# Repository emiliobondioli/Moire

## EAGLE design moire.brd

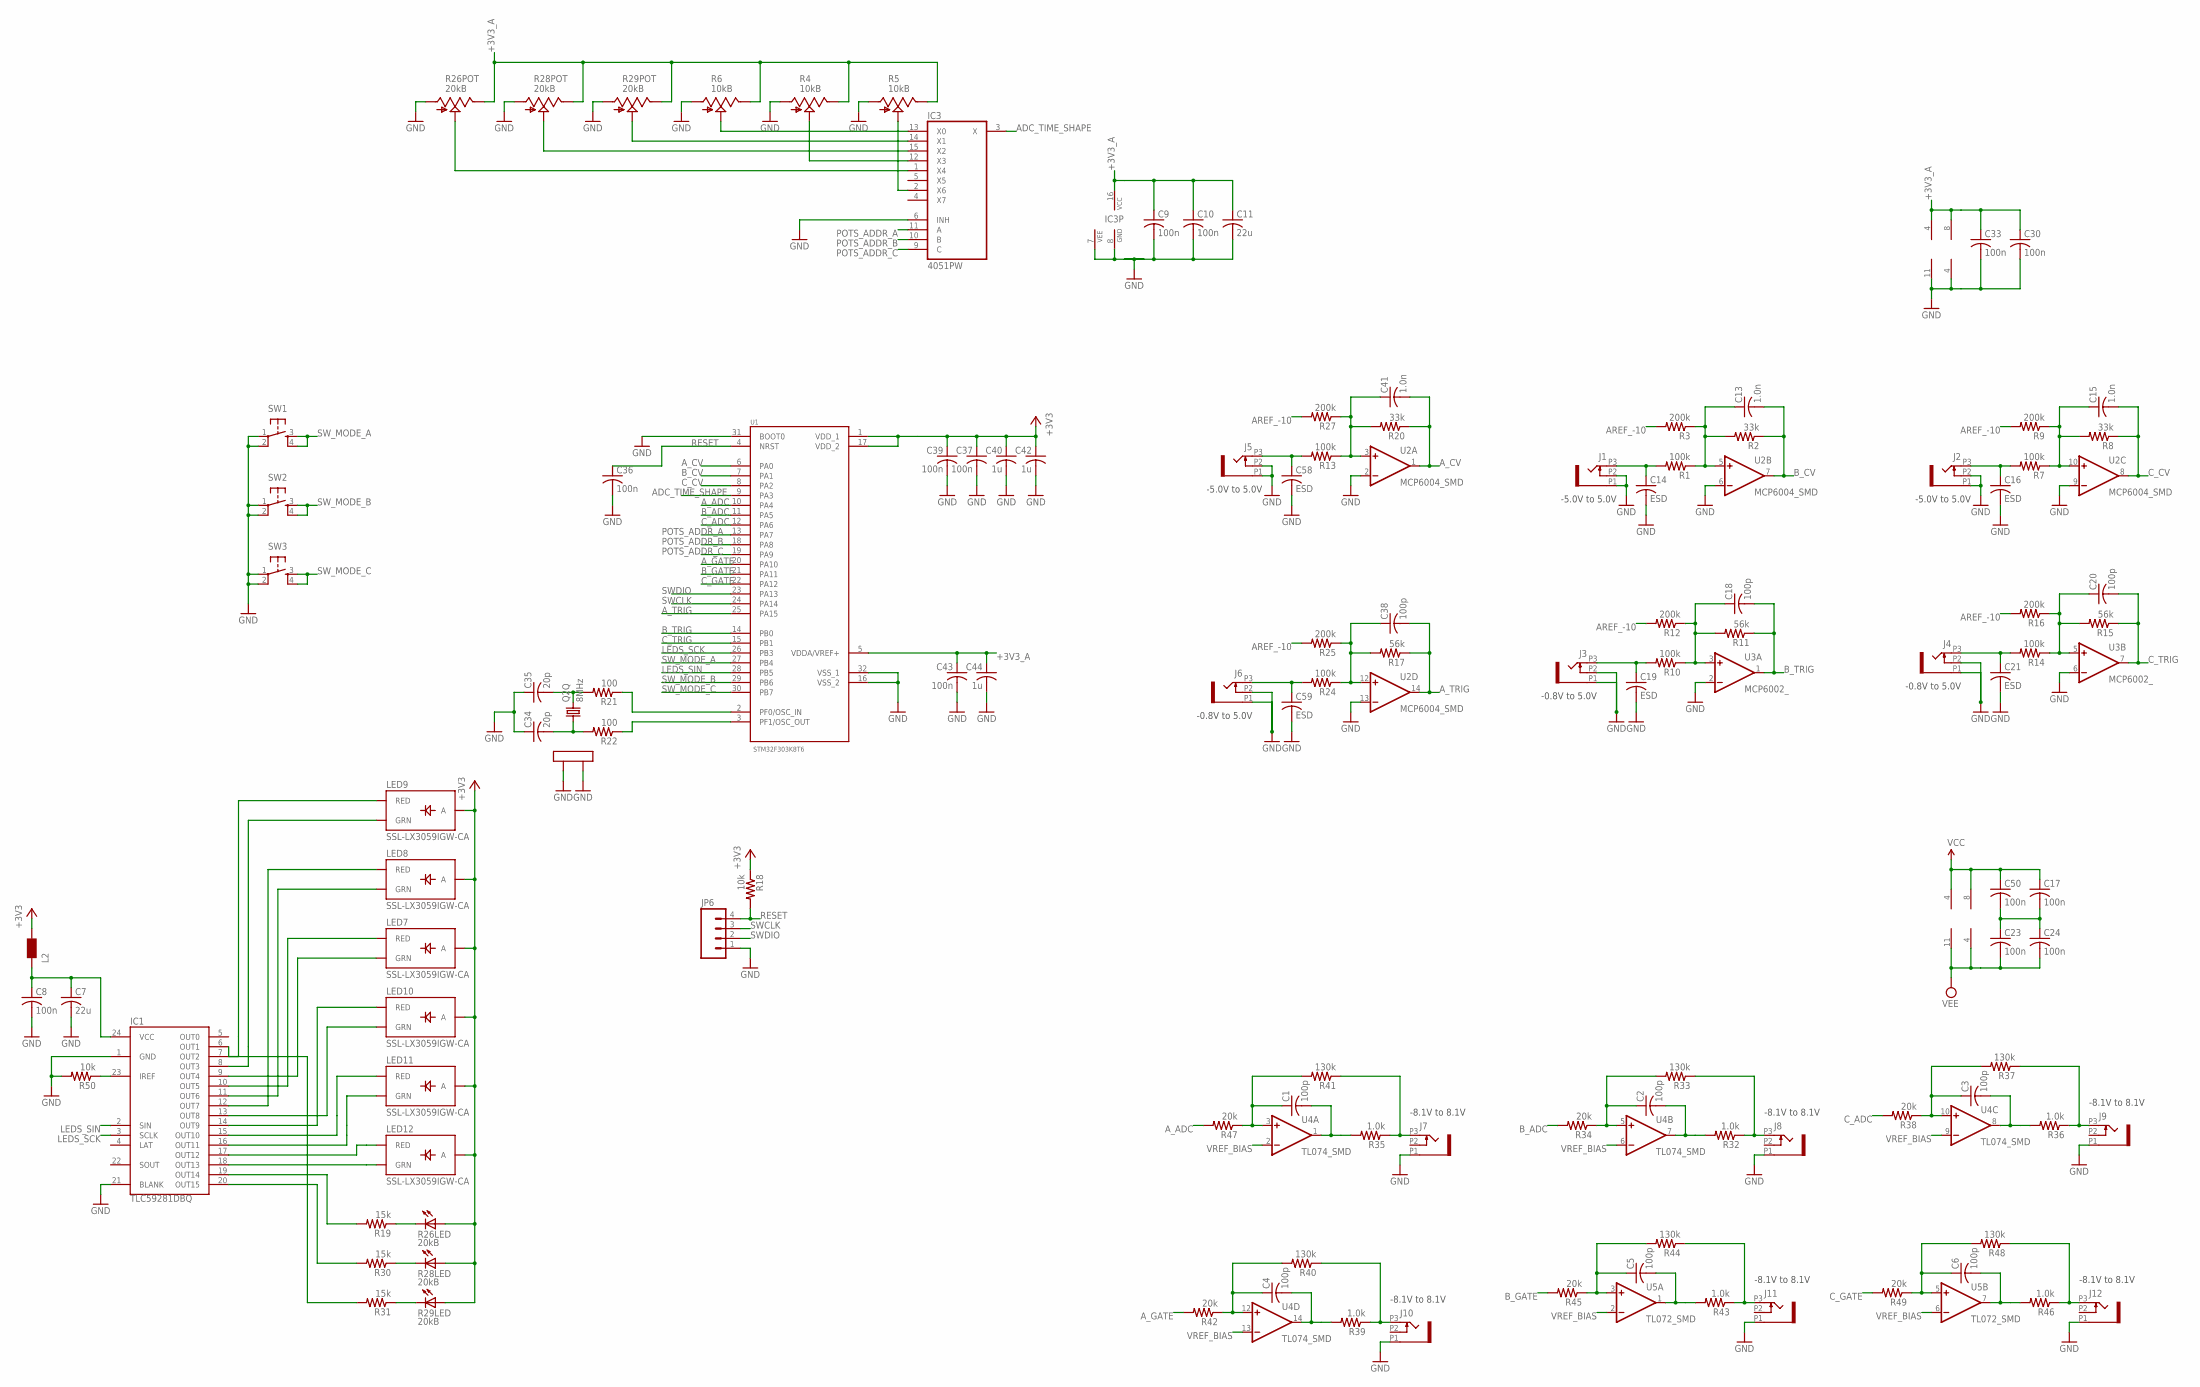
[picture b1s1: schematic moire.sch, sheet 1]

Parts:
C1, C2, C3, C4, C5, C6, C18, C20, C38: 100p; C0402
C7, C11: 22u; C1206
C8, C9, C10, C17, C23, C24, C30, C33, C36, C37, C39, C43, C50: 100n; C0402
C13, C15, C41: 1.0n; C0402
C14, C16, C19, C21, C58, C59: ESD; C0603
C34, C35: 20p; C0402
C40, C42, C44: 1u; C0402
IC1: TLC59281DBQ; TSSOP24_0635
IC3: 4051PW; TSSOP16_065
J1, J2, J3, J4, J5, J6, J7, J8, J9, J10, J11, J12: PJ301_THONKICONN6; WQP_PJ_301M6
JP6: M04PTH; 1X04
L2: WE-CBF_0603; 0603
LED7, LED8, LED9, LED10, LED11, LED12: SSL-LX3059IGW-CA; LED-BICOLOR-THROUGHHOLE-LUMEX
Q2: 8MHz; CTS406
R1, R7, R10, R13, R14, R24: 100k; R0402
R2, R8, R20: 33k; R0402
R3, R9, R12, R16, R25, R27: 200k; R0402
R4, R5, R6: 10kB; ALPS_POT_VERTICAL_PS
R11, R15, R17: 56k; R0402
R18, R50: 10k; R0402
R19, R30, R31: 15k; R0402
R21, R22: 100; R0402
R26, R28, R29: 20kB; BOURNS_SLIDER
R32, R35, R36, R39, R43, R46: 1.0k; R0603
R33, R37, R40, R41, R44, R48: 130k; R0402
R34, R38, R42, R45, R47, R49: 20k; R0402
SW1, SW2, SW3: TAC_SWITCHPTH; TACTILE-PTH
U1: STM32F303K8T6; QFP80P900X900X160-32N
U2: MCP6004_SMD; SO14
U3: MCP6002_; SO08
U4: TL074_SMD; SO14
U5: TL072_SMD; SO08

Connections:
+3V3_A: C9.1, C10.1, C11.1, C30.1, C33.1, C43.1, C44.1, IC3.16 (VCC), R4.P$1 (E), R5.P$1 (E), R6.P$1 (E), R26.3 (E), R28.3 (E), R29.3 (E), U1.5 (VDDA/VREF+), U2.4 (V+), U3.8 (V+); also elsewhere on the board
ADC_TIME_SHAPE: IC3.3 (X), U1.9 (PA3)
AREF_-10: R3.2, R9.2, R12.2, R16.2, R25.2, R27.2; also elsewhere on the board
A_ADC: R47.2, U1.10 (PA4)
A_CV: C41.2, R20.1, U1.6 (PA0), U2.1 (OUT)
A_GATE: R42.2, U1.20 (PA10)
A_TRIG: C38.2, R17.1, U1.25 (PA15), U2.14 (OUT)
B_ADC: R34.2, U1.11 (PA5)
B_CV: C13.2, R2.1, U1.7 (PA1), U2.7 (OUT)
B_GATE: R45.2, U1.21 (PA11)
B_TRIG: C18.2, R11.1, U1.14 (PB0), U3.1 (OUT)
C_ADC: R38.2, U1.12 (PA6)
C_CV: C15.2, R8.1, U1.8 (PA2), U2.8 (OUT)
C_GATE: R49.2, U1.22 (PA12)
C_TRIG: C20.2, R15.1, U1.15 (PB1), U3.7 (OUT)
GATE_IN1: C59.1, J6.P3 (3), R24.2
GATE_IN2: C19.1, J3.P3 (3), R10.2
GATE_IN3: C21.1, J4.P3 (3), R14.2
GND: C7.2, C8.2, C9.2, C10.2, C11.2, C14.2, C16.2, C19.2, C21.2, C30.2, C33.2, C34.1, C35.1, C36.2, C37.2, C39.2, C40.2, C42.2, C43.2, C44.2, C58.2, C59.2, IC1.1 (GND), IC1.21 (BLANK), IC3.6 (INH), IC3.7 (VEE), IC3.8 (GND), J1.P1 (1), J1.P2 (2), J2.P1 (1), J2.P2 (2), J3.P1 (1), J3.P2 (2), J4.P1 (1), J4.P2 (2), J5.P1 (1), J5.P2 (2), J6.P1 (1), J6.P2 (2), J7.P1 (1), J8.P1 (1), J9.P1 (1), J10.P1 (1), J11.P1 (1), J12.P1 (1), JP6.1, Q2.2 (LID1), Q2.4 (LID2), R4.P$3 (A), R5.P$3 (A), R6.P$3 (A), R26.1 (A), R28.1 (A), R29.1 (A), R50.2, SW1.1, SW1.2, SW2.1, SW2.2, SW3.1, SW3.2, U1.16 (VSS_2), U1.31 (BOOT0), U1.32 (VSS_1), U2.2 (-IN), U2.6 (-IN), U2.9 (-IN), U2.11 (V-), U2.13 (-IN), U3.2 (-IN), U3.4 (V-), U3.6 (-IN); also elsewhere on the board
HARMONICS_IN: C58.1, J5.P3 (3), R13.2
HARMONICS_IN1: C14.1, J1.P3 (3), R1.2
HARMONICS_IN2: C16.1, J2.P3 (3), R7.2
LEDS_SCK: IC1.3 (SCLK), U1.26 (PB3)
LEDS_SIN: IC1.2 (SIN), U1.28 (PB5)
unnamed: R29.E (C), R31.1
unnamed: C13.1, R1.1, R2.2, R3.1, U2.5 (+IN)
unnamed: C15.1, R7.1, R8.2, R9.1, U2.10 (+IN)
unnamed: C18.1, R10.1, R11.2, R12.1, U3.3 (+IN)
unnamed: C38.1, R17.2, R24.1, R25.1, U2.12 (+IN)
unnamed: C20.1, R14.1, R15.2, R16.1, U3.5 (+IN)
unnamed: J8.P3 (3), R32.1, R33.1
unnamed: C2.1, R33.2, R34.1, U4.5 (+IN)
unnamed: R21.1, U1.2 (PF0/OSC_IN)
unnamed: R22.1, U1.3 (PF1/OSC_OUT)
unnamed: C35.2, Q2.3 (2), R21.2
unnamed: C34.2, Q2.1, R22.2
unnamed: C2.2, R32.2, U4.7 (OUT)
unnamed: J9.P3 (3), R36.1, R37.1
unnamed: C3.1, R37.2, R38.1, U4.10 (+IN)
unnamed: C3.2, R36.2, U4.8 (OUT)
unnamed: J10.P3 (3), R39.1, R40.1
unnamed: C4.1, R40.2, R42.1, U4.12 (+IN)
unnamed: C4.2, R39.2, U4.14 (OUT)
unnamed: J11.P3 (3), R43.1, R44.1
unnamed: C5.1, R44.2, R45.1, U5.3 (+IN)
unnamed: C5.2, R43.2, U5.1 (OUT)
unnamed: J12.P3 (3), R46.1, R48.1
unnamed: C6.1, R48.2, R49.1, U5.5 (+IN)
unnamed: C6.2, R46.2, U5.7 (OUT)
unnamed: IC1.11 (OUT6), LED8.GREEN_C (GRN)
unnamed: IC1.10 (OUT5), LED7.RED_C (RED)
unnamed: IC1.12 (OUT7), LED8.RED_C (RED)
unnamed: IC1.7 (OUT2), LED9.RED_C (RED)
unnamed: IC1.8 (OUT3), LED9.GREEN_C (GRN)
unnamed: IC1.15 (OUT10), LED11.RED_C (RED)
unnamed: IC1.16 (OUT11), LED11.GREEN_C (GRN)
unnamed: IC1.13 (OUT8), LED10.GREEN_C (GRN)
unnamed: IC1.17 (OUT12), LED12.RED_C (RED)
unnamed: C41.1, R13.1, R20.2, R27.1, U2.3 (+IN)
unnamed: IC1.18 (OUT13), LED12.GREEN_C (GRN)
unnamed: IC1.14 (OUT9), LED10.RED_C (RED)
unnamed: C7.1, C8.1, IC1.24 (VCC), L2.1
unnamed: IC1.19 (OUT14), R19.2
unnamed: IC1.20 (OUT15), R30.2
unnamed: IC1.6 (OUT1), R31.2
unnamed: IC3.1 (X4), R26.2 (S)
unnamed: R28.E (C), R30.1
unnamed: R19.1, R26.E (C)
unnamed: IC3.2 (X6), R5.P$2 (S)
unnamed: C17.2, C23.1, C24.1, C50.2
unnamed: IC3.12 (X3), R4.P$2 (S)
unnamed: IC3.13 (X0), R6.P$2 (S)
unnamed: IC3.14 (X1), R29.2 (S)
unnamed: IC3.15 (X2), R28.2 (S)
unnamed: IC1.23 (IREF), R50.1
unnamed: J7.P3 (3), R35.1, R41.1
unnamed: C1.1, R41.2, R47.1, U4.3 (+IN)
unnamed: C1.2, R35.2, U4.1 (OUT)
unnamed: IC1.9 (OUT4), LED7.GREEN_C (GRN)
POTS_ADDR_A: IC3.11 (A), U1.13 (PA7)
POTS_ADDR_B: IC3.10 (B), U1.18 (PA8)
POTS_ADDR_C: IC3.9 (C), U1.19 (PA9)
RESET: C36.1, JP6.4, R18.2, U1.4 (NRST)
SWCLK: JP6.3, U1.24 (PA14)
SWDIO: JP6.2, U1.23 (PA13)
SW_MODE_A: SW1.3, SW1.4, U1.27 (PB4)
SW_MODE_B: SW2.3, SW2.4, U1.29 (PB6)
SW_MODE_C: SW3.3, SW3.4, U1.30 (PB7)
VCC: C17.1, C50.1, U4.4 (V+), U5.8 (V+); also elsewhere on the board
VEE: C23.2, C24.2, U4.11 (V-), U5.4 (V-); also elsewhere on the board
VREF_BIAS: U4.2 (-IN), U4.6 (-IN), U4.9 (-IN), U4.13 (-IN), U5.2 (-IN), U5.6 (-IN)

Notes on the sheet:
-5.0V to 5.0V
-0.8V to 5.0V
-8.1V to 8.1V

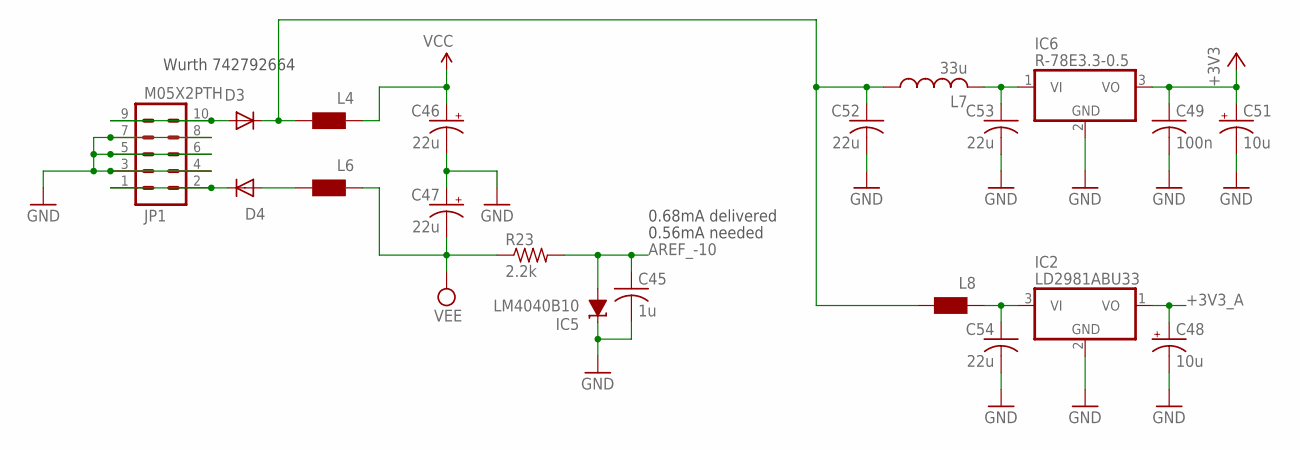
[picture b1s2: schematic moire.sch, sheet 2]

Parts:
C45: 1u; C0402
C46, C47: 22u; PANASONIC_B
C48, C51: 10u; PANASONIC_A
C49: 100n; C0402
C52, C53, C54: 22u; C1206
D3, D4: 1N5819HW; SOD123
IC2: LD2981ABU33; SOT89
IC5: LM4040B10; DBZ_R-PDSO-G3
IC6: R-78E3.3-0.5; WE78
JP1: M05X2PTH; 2X5-PTH
L4, L6, L8: WE-CBF_0603; 0603
L7: 33u; L2012C
R23: 2.2k; R0402

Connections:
+3V3_A: C48.+, IC2.1 (VO); also elsewhere on the board
AREF_-10: C45.1, IC5.2 (A), R23.2; also elsewhere on the board
GND: C45.2, C46.-, C47.+, C48.-, C49.2, C51.-, C52.2, C53.2, C54.2, IC2.2 (GND), IC5.1 (C), IC6.2 (GND), JP1.3, JP1.4, JP1.5, JP1.6, JP1.7, JP1.8; also elsewhere on the board
unnamed: D3.A, JP1.9, JP1.10
unnamed: D4.C, JP1.1, JP1.2
unnamed: C53.1, IC6.1 (VI), L7.2
unnamed: D4.A, L6.2
unnamed: C52.1, D3.C, L4.2, L7.1, L8.2
unnamed: C54.1, IC2.3 (VI), L8.1
VCC: C46.+, L4.1; also elsewhere on the board
VEE: C47.-, L6.1, R23.1; also elsewhere on the board

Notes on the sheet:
0.56mA needed
Wurth 742792664
0.68mA delivered

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
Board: 2 copper layers, 138 parts (3 on the bottom side), 98 nets, no tracks yet.

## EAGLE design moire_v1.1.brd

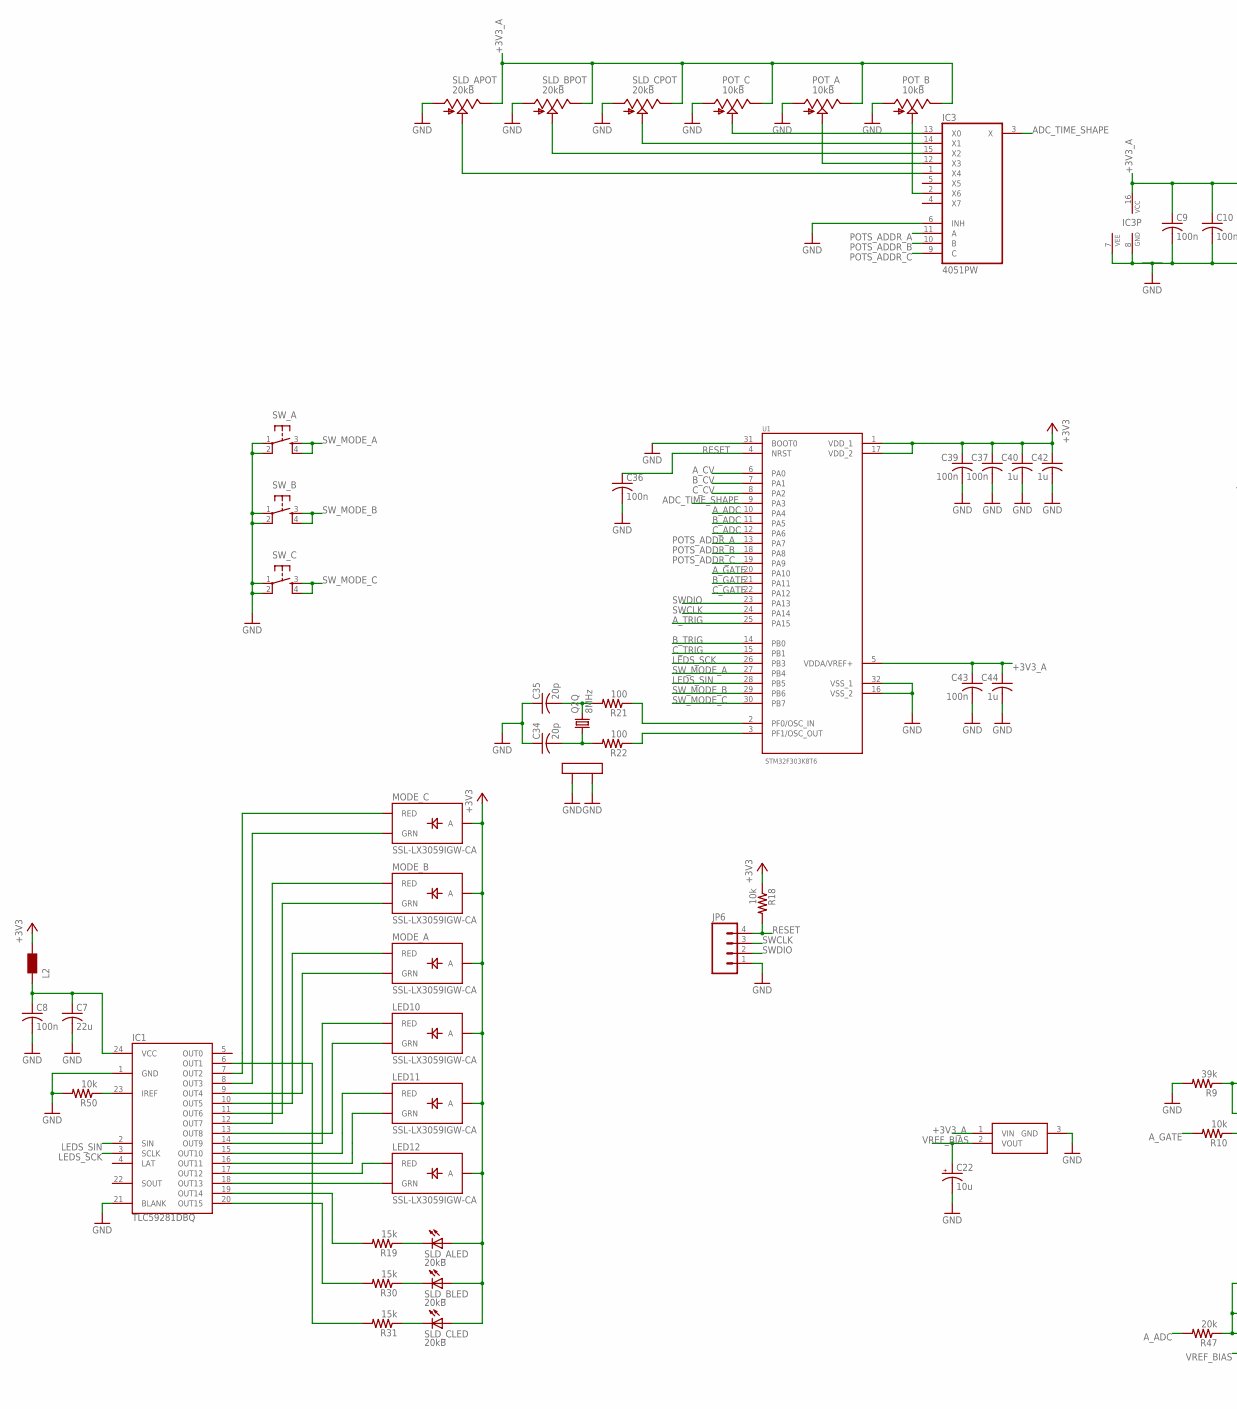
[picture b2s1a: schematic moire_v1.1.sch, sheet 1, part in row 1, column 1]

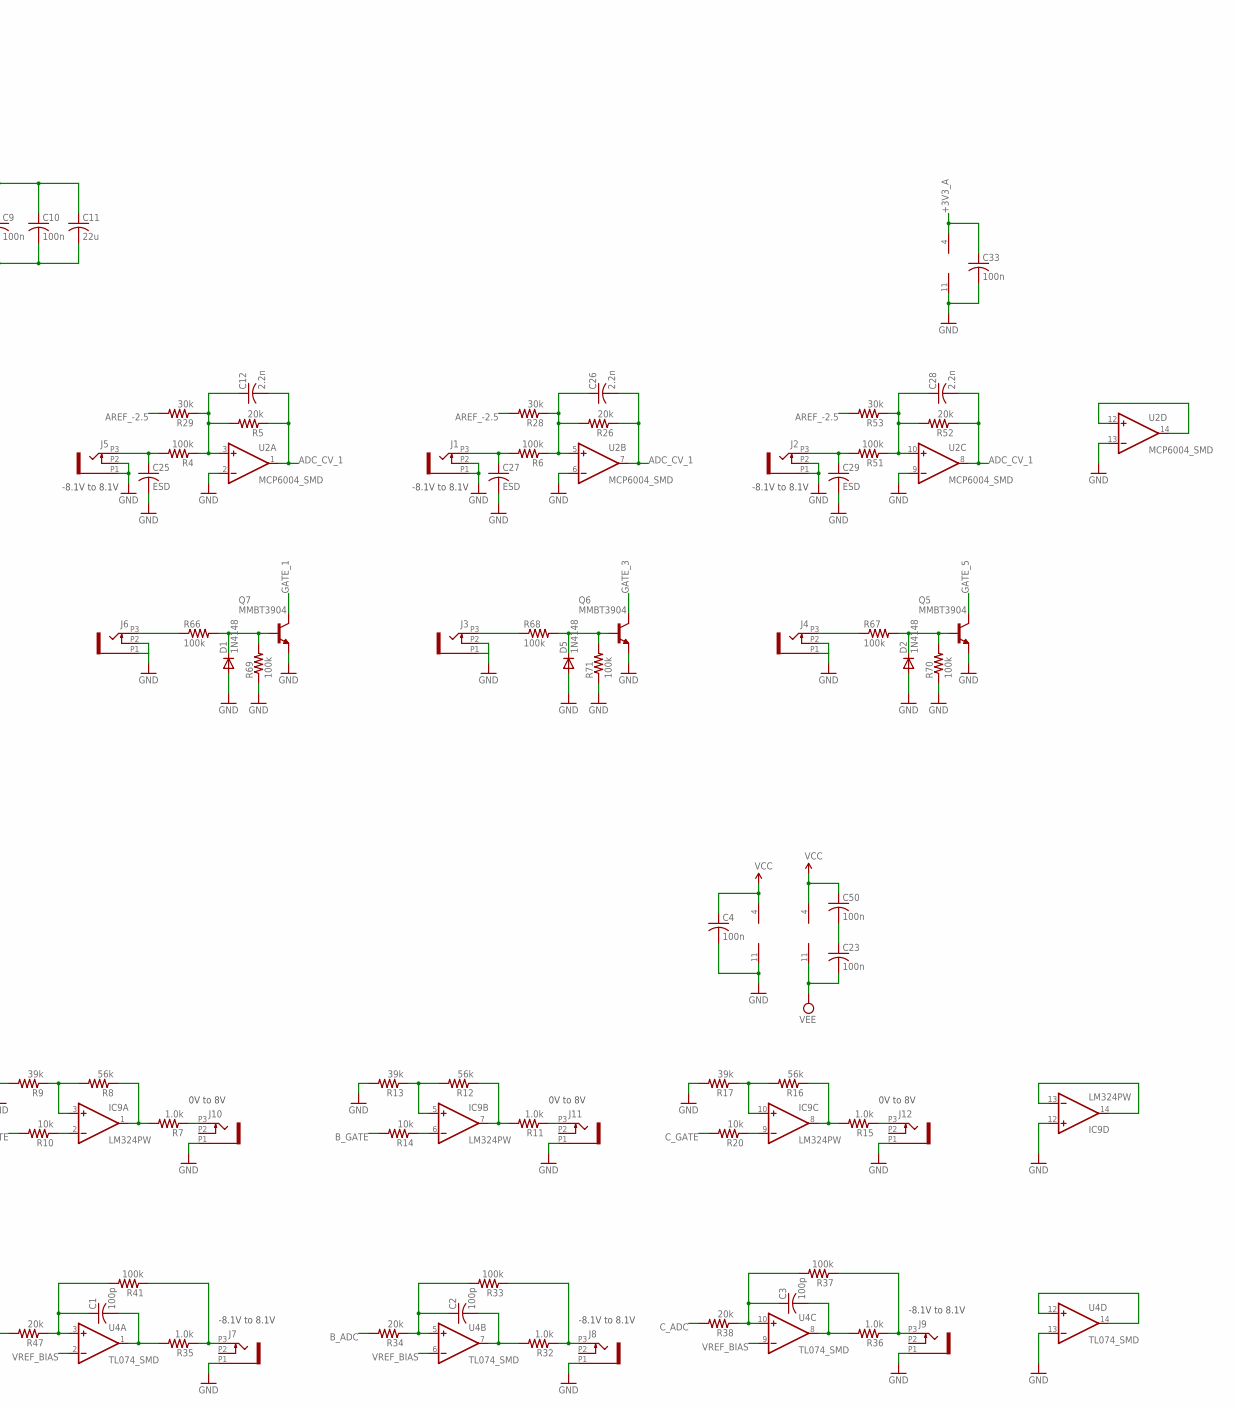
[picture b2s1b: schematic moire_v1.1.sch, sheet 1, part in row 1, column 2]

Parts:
C1, C2, C3: 100p; C0603
C4: 100n; C0402
C7, C11: 22u; C1206
C8, C9, C10, C23, C33, C36, C37, C39, C43, C50: 100n; C0603
C12, C26, C28: 2.2n; C0402
C22: 10u; PANASONIC_A
C25, C27, C29: ESD; C0603
C34, C35: 20p; C0603
C40, C42, C44: 1u; C0603
D1, D2, D5: 1N4148; SOD523
IC1: TLC59281DBQ; TSSOP24_0635
IC3: 4051PW; TSSOP16_065
IC4, IC9: LM324PW; TSSOP14_065
J1, J2, J3, J4, J5, J6, J7, J8, J9, J10, J11, J12: PJ301_THONKICONN6; WQP_PJ_301M6
JP6: M04PTH; 1X04
L2: WE-CBF_0603; 0603
LED10, LED11, LED12: SSL-LX3059IGW-CA; LED-BICOLOR-THROUGHHOLE-LUMEX
MODE_A: SSL-LX3059IGW-CA; LED-BICOLOR-THROUGHHOLE-LUMEX
MODE_B: SSL-LX3059IGW-CA; LED-BICOLOR-THROUGHHOLE-LUMEX
MODE_C: SSL-LX3059IGW-CA; LED-BICOLOR-THROUGHHOLE-LUMEX
POT_A: 10kB; ALPS_POT_VERTICAL_PS
POT_B: 10kB; ALPS_POT_VERTICAL_PS
POT_C: 10kB; ALPS_POT_VERTICAL_PS
Q2: 8MHz; CTS406
Q5, Q6, Q7: MMBT3904; SOT23-BEC
R4, R6, R51, R66, R67, R68, R69, R70, R71: 100k; R0402
R5, R26, R52: 20k; R0402
R7, R11, R15, R32, R35, R36: 1.0k; R0603
R8, R12, R16: 56k; R0402
R9, R13, R17: 39k; R0402
R10, R14, R20: 10k; R0402
R18, R50: 10k; R0603
R19, R30, R31: 15k; R0603
R21, R22: 100; R0603
R28, R29, R53: 30k; R0402
R33, R37, R41: 100k; R0603
R34, R38, R47: 20k; R0603
SLD_A: 20kB; BOURNS_SLIDER
SLD_B: 20kB; BOURNS_SLIDER
SLD_C: 20kB; BOURNS_SLIDER
SW_A: TAC_SWITCHPTH; TACTILE-PTH
SW_B: TAC_SWITCHPTH; TACTILE-PTH
SW_C: TAC_SWITCHPTH; TACTILE-PTH
U1: STM32F303K8T6; QFP80P900X900X160-32N
U2: MCP6004_SMD; SO14
U4: TL074_SMD; SO14
U$1: ISL21010; SOT-23-3

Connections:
+3V3: C37.1, C39.1, C40.1, C42.1, L2.2, LED10.A, LED11.A, LED12.A, MODE_A.A, MODE_B.A, MODE_C.A, R18.1, SLD_A.B (A), SLD_B.B (A), SLD_C.B (A), U1.1 (VDD_1), U1.17 (VDD_2); also elsewhere on the board
+3V3_A: C9.1, C10.1, C11.1, C33.1, C43.1, C44.1, IC3.16 (VCC), POT_A.P$1 (E), POT_B.P$1 (E), POT_C.P$1 (E), SLD_A.3 (E), SLD_B.3 (E), SLD_C.3 (E), U1.5 (VDDA/VREF+), U2.4 (V+), U$1.1 (VIN); also elsewhere on the board
ADC_CV_1: C12.2, C26.2, C28.2, R5.1, R26.1, R52.1, U2.1 (OUT), U2.7 (OUT), U2.8 (OUT)
ADC_TIME_SHAPE: IC3.3 (X), U1.9 (PA3)
AREF_-2.5: R28.2, R29.2, R53.2; also elsewhere on the board
A_ADC: R47.2, U1.10 (PA4)
A_CV: U1.6 (PA0)
A_GATE: R10.2, U1.20 (PA10)
A_TRIG: U1.25 (PA15)
B_ADC: R34.2, U1.11 (PA5)
B_CV: U1.7 (PA1)
B_GATE: R14.2, U1.21 (PA11)
B_TRIG: U1.14 (PB0)
C_ADC: R38.2, U1.12 (PA6)
C_CV: U1.8 (PA2)
C_GATE: R20.2, U1.22 (PA12)
C_TRIG: U1.15 (PB1)
GATE_1: Q7.C
GATE_3: Q6.C
GATE_5: Q5.C
GND: C4.2, C7.2, C8.2, C9.2, C10.2, C11.2, C22.-, C25.2, C27.2, C29.2, C33.2, C34.1, C35.1, C36.2, C37.2, C39.2, C40.2, C42.2, C43.2, C44.2, D1.A, D2.A, D5.A, IC1.1 (GND), IC1.21 (BLANK), IC3.6 (INH), IC3.7 (VEE), IC3.8 (GND), IC4.11 (V-), IC9.12 (+IN), J1.P1 (1), J1.P2 (2), J2.P1 (1), J2.P2 (2), J3.P1 (1), J3.P2 (2), J4.P1 (1), J4.P2 (2), J5.P1 (1), J5.P2 (2), J6.P1 (1), J6.P2 (2), J7.P1 (1), J8.P1 (1), J9.P1 (1), J10.P1 (1), J11.P1 (1), J12.P1 (1), JP6.1, POT_A.P$3 (A), POT_B.P$3 (A), POT_C.P$3 (A), Q2.2 (LID1), Q2.4 (LID2), Q5.E, Q6.E, Q7.E, R9.2, R13.2, R17.2, R50.2, R69.1, R70.1, R71.1, SLD_A.1 (A), SLD_B.1 (A), SLD_C.1 (A), SW_A.1, SW_A.2, SW_B.1, SW_B.2, SW_C.1, SW_C.2, U1.16 (VSS_2), U1.31 (BOOT0), U1.32 (VSS_1), U2.2 (-IN), U2.6 (-IN), U2.9 (-IN), U2.11 (V-), U2.13 (-IN), U4.13 (-IN), U$1.3 (GND); also elsewhere on the board
LEDS_SCK: IC1.3 (SCLK), U1.26 (PB3)
LEDS_SIN: IC1.2 (SIN), U1.28 (PB5)
MORPH_IN: C25.1, J5.P3 (3), R4.2
MORPH_IN1: C27.1, J1.P3 (3), R6.2
MORPH_IN2: C29.1, J2.P3 (3), R51.2
unnamed: R31.1, SLD_C.E (C)
unnamed: J6.P3 (3), R66.1
unnamed: IC9.13 (-IN), IC9.14 (OUT)
unnamed: J8.P3 (3), R32.1, R33.1
unnamed: C2.1, R33.2, R34.1, U4.5 (+IN)
unnamed: R21.1, U1.2 (PF0/OSC_IN)
unnamed: R22.1, U1.3 (PF1/OSC_OUT)
unnamed: C35.2, Q2.3 (2), R21.2
unnamed: C34.2, Q2.1, R22.2
unnamed: U2.12 (+IN), U2.14 (OUT)
unnamed: U4.12 (+IN), U4.14 (OUT)
unnamed: IC9.1 (OUT), R7.2, R8.1
unnamed: C2.2, R32.2, U4.7 (OUT)
unnamed: J9.P3 (3), R36.1, R37.1
unnamed: C3.1, R37.2, R38.1, U4.10 (+IN)
unnamed: C3.2, R36.2, U4.8 (OUT)
unnamed: J10.P3 (3), R7.1
unnamed: IC9.3 (+IN), R8.2, R9.1
unnamed: IC9.2 (-IN), R10.1
unnamed: IC9.7 (OUT), R11.2, R12.1
unnamed: J11.P3 (3), R11.1
unnamed: IC9.5 (+IN), R12.2, R13.1
unnamed: IC9.6 (-IN), R14.1
unnamed: IC9.8 (OUT), R15.2, R16.1
unnamed: J12.P3 (3), R15.1
unnamed: IC1.11 (OUT6), MODE_B.GREEN_C (GRN)
unnamed: IC1.10 (OUT5), MODE_A.RED_C (RED)
unnamed: IC1.12 (OUT7), MODE_B.RED_C (RED)
unnamed: IC1.7 (OUT2), MODE_C.RED_C (RED)
unnamed: IC1.8 (OUT3), MODE_C.GREEN_C (GRN)
unnamed: IC1.15 (OUT10), LED11.RED_C (RED)
unnamed: IC1.16 (OUT11), LED11.GREEN_C (GRN)
unnamed: IC1.13 (OUT8), LED10.GREEN_C (GRN)
unnamed: IC1.17 (OUT12), LED12.RED_C (RED)
unnamed: D1.C, Q7.B, R66.2, R69.2
unnamed: IC1.18 (OUT13), LED12.GREEN_C (GRN)
unnamed: IC1.14 (OUT9), LED10.RED_C (RED)
unnamed: C7.1, C8.1, IC1.24 (VCC), L2.1
unnamed: IC1.19 (OUT14), R19.2
unnamed: IC1.20 (OUT15), R30.2
unnamed: IC1.6 (OUT1), R31.2
unnamed: IC3.1 (X4), SLD_A.2 (S)
unnamed: R30.1, SLD_B.E (C)
unnamed: R19.1, SLD_A.E (C)
unnamed: IC3.2 (X6), POT_B.P$2 (S)
unnamed: C23.1, C50.2
unnamed: IC3.12 (X3), POT_A.P$2 (S)
unnamed: IC3.13 (X0), POT_C.P$2 (S)
unnamed: IC3.14 (X1), SLD_C.2 (S)
unnamed: IC3.15 (X2), SLD_B.2 (S)
unnamed: C12.1, R4.1, R5.2, R29.1, U2.3 (+IN)
unnamed: C26.1, R6.1, R26.2, R28.1, U2.5 (+IN)
unnamed: C28.1, R51.1, R52.2, R53.1, U2.10 (+IN)
unnamed: J3.P3 (3), R68.1
unnamed: IC9.10 (+IN), R16.2, R17.1
unnamed: D5.C, Q6.B, R68.2, R71.2
unnamed: J4.P3 (3), R67.1
unnamed: IC9.9 (-IN), R20.1
unnamed: D2.C, Q5.B, R67.2, R70.2
unnamed: IC1.23 (IREF), R50.1
unnamed: J7.P3 (3), R35.1, R41.1
unnamed: C1.1, R41.2, R47.1, U4.3 (+IN)
unnamed: C1.2, R35.2, U4.1 (OUT)
unnamed: IC1.9 (OUT4), MODE_A.GREEN_C (GRN)
POTS_ADDR_A: IC3.11 (A), U1.13 (PA7)
POTS_ADDR_B: IC3.10 (B), U1.18 (PA8)
POTS_ADDR_C: IC3.9 (C), U1.19 (PA9)
RESET: C36.1, JP6.4, R18.2, U1.4 (NRST)
SWCLK: JP6.3, U1.24 (PA14)
SWDIO: JP6.2, U1.23 (PA13)
SW_MODE_A: SW_A.3, SW_A.4, U1.27 (PB4)
SW_MODE_B: SW_B.3, SW_B.4, U1.29 (PB6)
SW_MODE_C: SW_C.3, SW_C.4, U1.30 (PB7)
V+: IC9.4 (V+)
V-: IC9.11 (V-)
VCC: C4.1, C50.1, IC4.4 (V+), U4.4 (V+); also elsewhere on the board
VEE: C23.2, U4.11 (V-); also elsewhere on the board
VREF_BIAS: C22.+, U4.2 (-IN), U4.6 (-IN), U4.9 (-IN), U$1.2 (VOUT)

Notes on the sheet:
-8.1V to 8.1V
0V to 8V

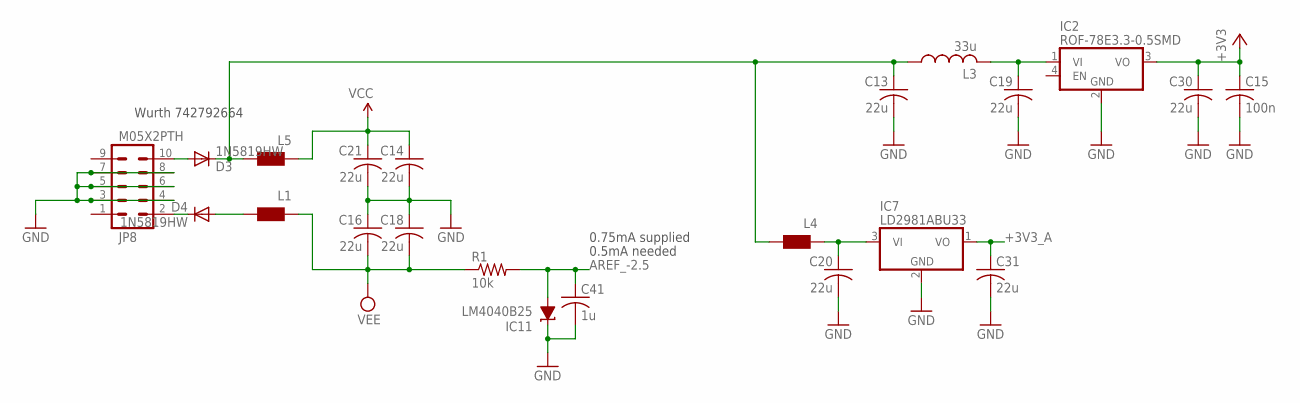
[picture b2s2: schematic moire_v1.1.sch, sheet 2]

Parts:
C13, C14, C16, C18, C19, C20, C21, C30, C31: 22u; C1206
C15: 100n; C0402
C41: 1u; C0402
D3, D4: 1N5819HW; SOD123
IC2: ROF-78E3.3-0.5SMD; ROF78EXX-0.5SMD
IC7: LD2981ABU33; SOT89
IC11: LM4040B25; DBZ_R-PDSO-G3
JP8: M05X2PTH; 2X5-PTH
L1, L4, L5: WE-CBF_0603; 0603
L3: 33u; L2012C
R1: 10k; R0402

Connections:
+3V3: C15.1, C30.1, IC2.3 (VO); also elsewhere on the board
+3V3_A: C31.1, IC7.1 (VO); also elsewhere on the board
AREF_-2.5: C41.1, IC11.2 (A), R1.2; also elsewhere on the board
GND: C13.2, C14.2, C15.2, C16.1, C18.1, C19.2, C20.2, C21.2, C30.2, C31.2, C41.2, IC2.2 (GND), IC7.2 (GND), IC11.1 (C), JP8.3, JP8.4, JP8.5, JP8.6, JP8.7, JP8.8; also elsewhere on the board
unnamed: D4.A, L1.2
unnamed: C13.1, D3.C, L3.1, L4.2, L5.2
unnamed: C20.1, IC7.3 (VI), L4.1
unnamed: D3.A, JP8.10
unnamed: D4.C, JP8.2
unnamed: C19.1, IC2.1 (VI), L3.2
VCC: C14.1, C21.1, L5.1; also elsewhere on the board
VEE: C16.2, C18.2, L1.1, R1.1; also elsewhere on the board

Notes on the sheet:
0.5mA needed
Wurth 742792664
0.75mA supplied

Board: 2 copper layers, 137 parts (2 on the bottom side), 99 nets, no tracks yet.
